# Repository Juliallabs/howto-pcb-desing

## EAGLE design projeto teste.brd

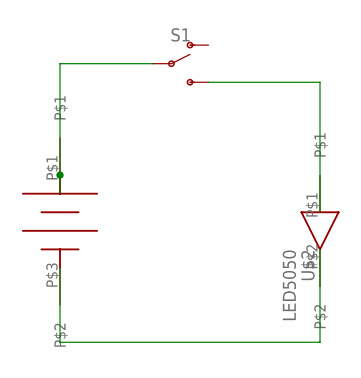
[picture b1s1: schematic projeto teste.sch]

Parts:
S1: SWITCH-SPDT-SMD-RIGHT-ANGLE; SWITCH_SPST_SMD_A
U$1: CR2025
U$2: LED5050

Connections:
unnamed: S1.2, U$1.P$1
unnamed: S1.3 (S), U$2.P$1
unnamed: U$1.P$3, U$2.P$2

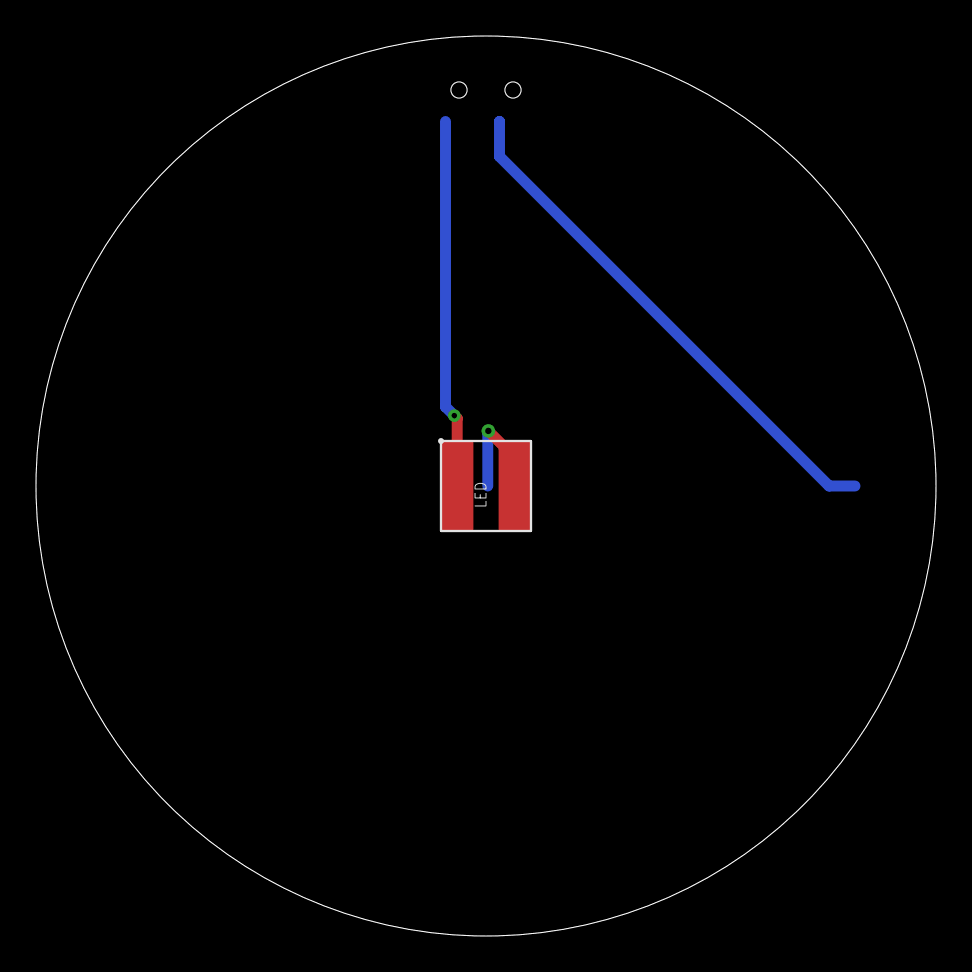
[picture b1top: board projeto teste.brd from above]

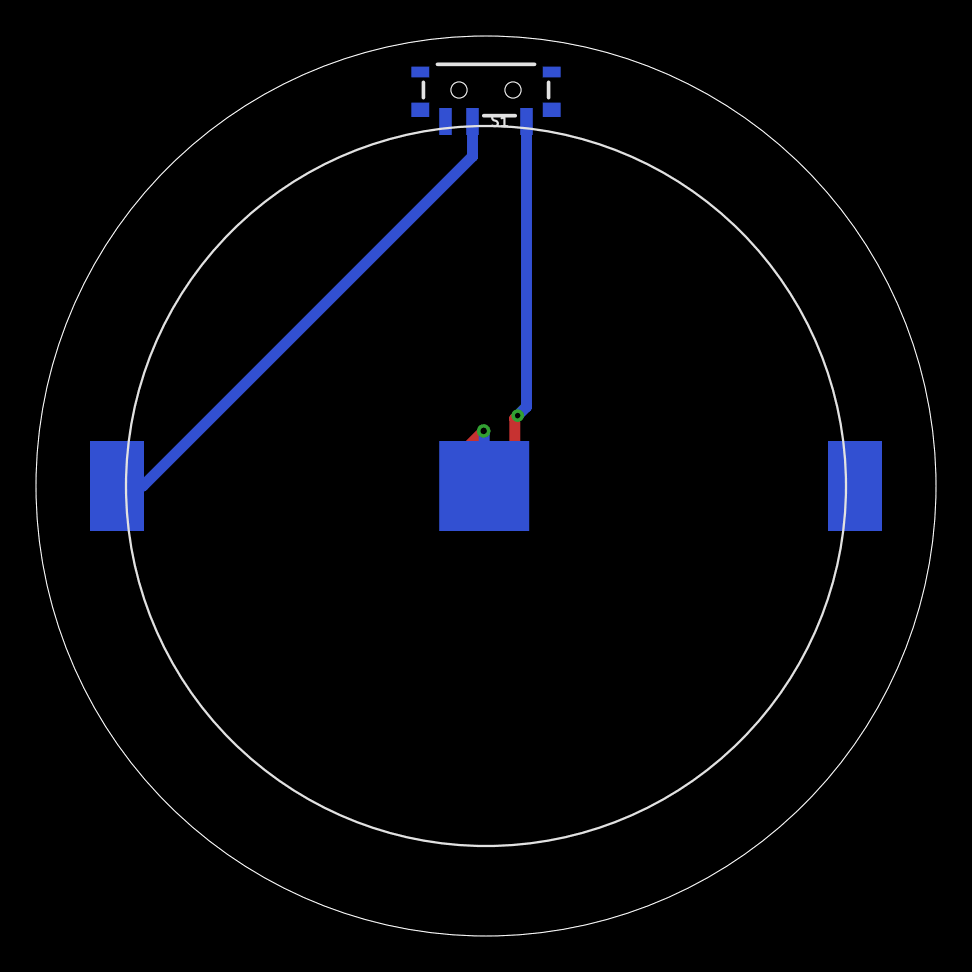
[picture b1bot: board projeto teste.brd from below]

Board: 2 copper layers, 50.0 x 50.0 mm, 3 parts (2 on the bottom side), 3 nets.

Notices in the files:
parts and their libraries:
PatternAgents-ProtoPads: License : http://creativecommons.org/licenses/by-sa/4.0
(Creative Commons 4.0)
